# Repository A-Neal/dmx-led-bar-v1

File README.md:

# FPGA DMX Decoder and PWM Driver Written in Verilog

This project directory is uploaded as-is, and doesn't contain a lot of polish.

I used Apio to build the Verilog into a configuration for the FPGA, and developed
on a Lattice iCE40UP5k. You can use the underlying toolchain if you'd prefer, but
I recommend Apio if you aren't looking to get into the weeds and just want to
modify little bits of the Verilog or build it for a different FPGA.

If you are building exactly according to what's in this repo, you don't need to
have Apio or build the configuration. **hardware.bin** is the file that is already
built and padded to fit into the 2Mbit flash on the PCB.

To flash, I used a generic CH341A USB SPI flasher with `flashrom` to flash the
hardware.bin file.

`$ flashrom -p ch341a_spi -w hardware.bin`

This repo includes the KiCAD project for the PCB, as well as just the gerber files
for have the PCB produced if you don't want to do any mods.

The BOM file is a list of everything that goes on the PCB and a link to the part
on Mouser. It's inside the KiCAD project directory.

The LED strips I used get a little too hot for the channels I used when everything
is turned up, so I'm not going to recommend them. But I will link them anyway
because they're excellent for other uses or if you're building a beefier fixture
than these plans are for.

LED Strip I Used: https://a.co/d/0fOELpNe

Less Powerful Equivalent LED Strip: https://a.co/d/0jd0L9jr

Aluminum Diffuser Channels: https://a.co/d/0e7rKbcg

24V Power Supply: https://a.co/d/09dPfuRe

Use any 12-24V LED strip and power supply that you want so long as the strip fits
in the channels, and the power supply can push enough power comfortably.

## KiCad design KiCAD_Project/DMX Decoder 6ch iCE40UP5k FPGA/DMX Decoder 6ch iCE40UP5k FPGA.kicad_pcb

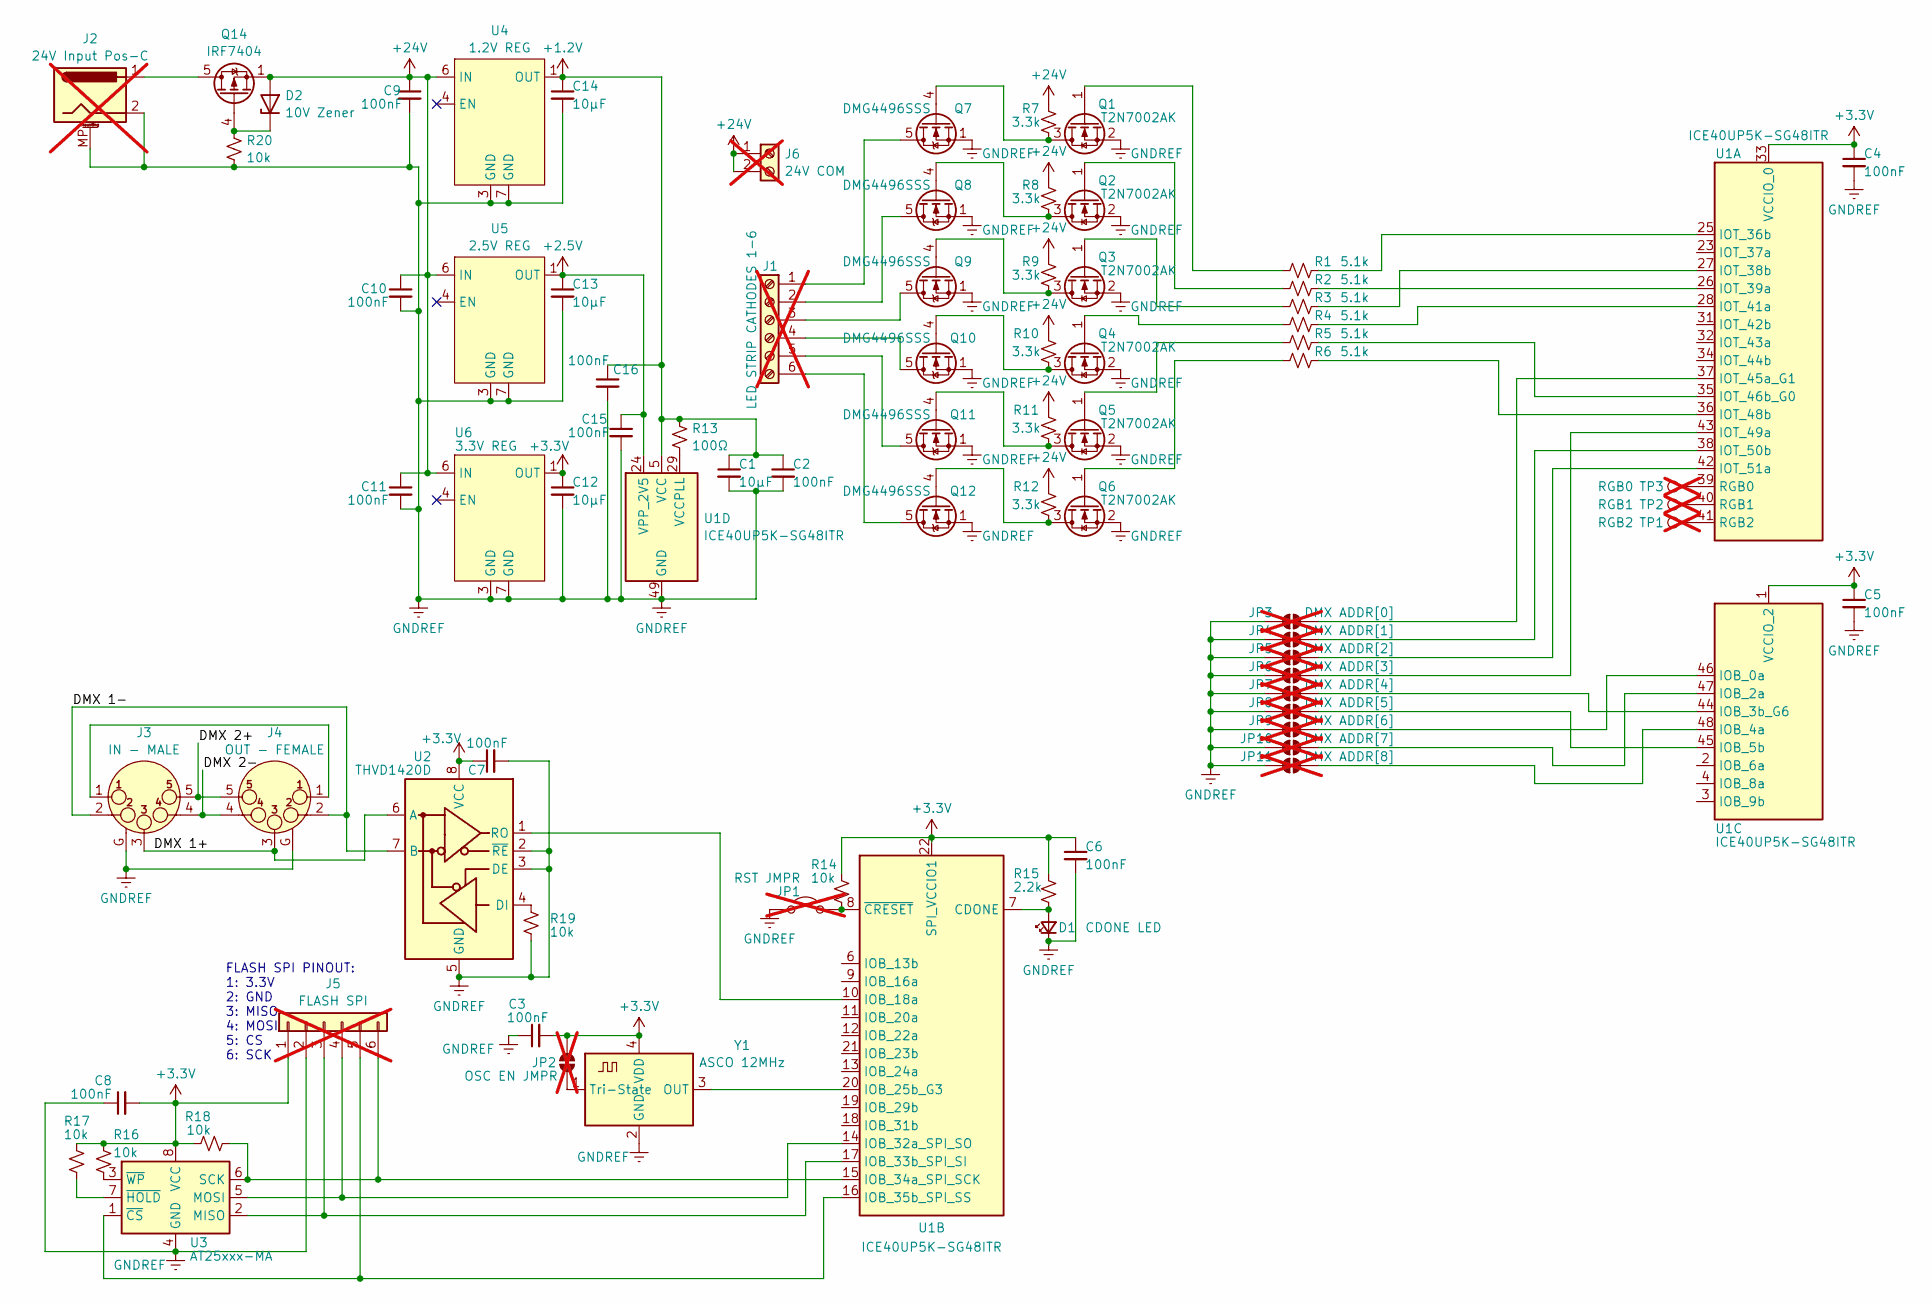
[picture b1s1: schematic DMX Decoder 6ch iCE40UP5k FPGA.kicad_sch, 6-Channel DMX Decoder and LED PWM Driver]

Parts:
C1, C12, C13, C14: 10μF; C_0603_1608Metric
C2, C3, C4, C5, C6, C7, C8, C9, C10, C11, C15, C16: 100nF; C_0603_1608Metric
D1: CDONE LED; LED_0805_2012Metric
D2: 10V Zener; D_SOD-123
J1: LED STRIP CATHODES 1-6; TerminalBlock_MaiXu_MX126-5.0-06P_1x06_P5.00mm; not fitted
J2: 24V Input Pos-C; BarrelJack_Horizontal_CUI_PJ-057A; not fitted
J3: IN - MALE; Jack_XLR_Neutrik_NC5MAV_Vertical
J4: OUT - FEMALE; Jack_XLR_Neutrik_NC5FAV_Vertical
J5: FLASH SPI; PinHeader_1x06_P2.54mm_Vertical; not fitted
J6: 24V COM; TerminalBlock_MaiXu_MX126-5.0-02P_1x02_P5.00mm; not fitted
JP1: RST JMPR; PinHeader_1x02_P1.27mm_Vertical; not fitted
JP2: OSC EN JMPR; SolderJumper-2_P1.3mm_Open_TrianglePad1.0x1.5mm; not fitted
JP3: DMX ADDR[0]; SolderJumper-2_P1.3mm_Open_TrianglePad1.0x1.5mm; not fitted
JP4: DMX ADDR[1]; SolderJumper-2_P1.3mm_Open_TrianglePad1.0x1.5mm; not fitted
JP5: DMX ADDR[2]; SolderJumper-2_P1.3mm_Open_TrianglePad1.0x1.5mm; not fitted
JP6: DMX ADDR[3]; SolderJumper-2_P1.3mm_Open_TrianglePad1.0x1.5mm; not fitted
JP7: DMX ADDR[4]; SolderJumper-2_P1.3mm_Open_TrianglePad1.0x1.5mm; not fitted
JP8: DMX ADDR[5]; SolderJumper-2_P1.3mm_Open_TrianglePad1.0x1.5mm; not fitted
JP9: DMX ADDR[6]; SolderJumper-2_P1.3mm_Open_TrianglePad1.0x1.5mm; not fitted
JP10: DMX ADDR[7]; SolderJumper-2_P1.3mm_Open_TrianglePad1.0x1.5mm; not fitted
JP11: DMX ADDR[8]; SolderJumper-2_P1.3mm_Open_TrianglePad1.0x1.5mm; not fitted
Q1, Q2, Q3, Q4, Q5, Q6: T2N7002AK; SOT-23
Q7, Q8, Q9, Q10, Q11, Q12: DMG4496SSS; SOIC-8_3.9x4.9mm_P1.27mm
Q14: IRF7404; SOIC-8_3.9x4.9mm_P1.27mm
R1, R2, R3, R4, R5, R6: 5.1k; R_0603_1608Metric
R7, R8, R9, R10, R11, R12: 3.3k; R_0603_1608Metric
R13: 100Ω; R_0603_1608Metric
R14, R16, R17, R18, R19, R20: 10k; R_0603_1608Metric
R15: 2.2k; R_0603_1608Metric
TP1: RGB2; Pin_D0.7mm_L6.5mm_W1.8mm_FlatFork; not fitted
TP2: RGB1; Pin_D0.7mm_L6.5mm_W1.8mm_FlatFork; not fitted
TP3: RGB0; Pin_D0.7mm_L6.5mm_W1.8mm_FlatFork; not fitted
U1: ICE40UP5K-SG48ITR; QFN-48-1EP_7x7mm_P0.5mm_EP5.6x5.6mm
U2: THVD1420D; SOIC-8_3.9x4.9mm_P1.27mm
U3: AT25xxx-MA; DFN-8-1EP_3x2mm_P0.5mm_EP1.75x1.45mm
U4: 1.2V REG; WSON-6-1EP_2x2mm_P0.65mm_EP1x1.6mm
U5: 2.5V REG; WSON-6-1EP_2x2mm_P0.65mm_EP1x1.6mm
U6: 3.3V REG; WSON-6-1EP_2x2mm_P0.65mm_EP1x1.6mm
Y1: ASCO 12MHz; Oscillator_SMD_Abracon_ASCO-4Pin_1.6x1.2mm

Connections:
+1.2V: C1.1, C2.1, C14.1, C16.1, R13.2, U1.5 (VCC), U1.30 (VCC), U4.1 (OUT)
+2.5V: C13.1, C15.1, U1.24 (VPP_2V5), U5.1 (OUT)
+3.3V: C3.2, C4.1, C5.1, C6.1, C7.1, C8.2, C12.1, J5.1, JP2.2 (B), R14.2, R15.2, R16.2, R17.2, R18.2, U1.1 (VCCIO_2), U1.22 (SPI_VCCIO1), U1.33 (VCCIO_0), U2.8 (VCC), U3.8 (VCC), U6.1 (OUT), Y1.4 (VDD)
+24V: C9.1, C10.1, C11.1, D2.2 (A), J6.1, J6.2, Q14.1 (S), Q14.2 (S), Q14.3 (S), R7.2, R8.2, R9.2, R10.2, R11.2, R12.2, U4.6 (IN), U5.6 (IN), U6.6 (IN)
/DMX 1+: J3.3, J4.3, U2.6 (A)
/DMX 1-: J3.2, J4.2, U2.7 (B)
/DMX 2+: J3.5, J4.5
/DMX 2-: J3.4 (P3), J4.4 (P3)
GNDREF: C1.2, C2.2, C3.1, C4.2, C5.2, C6.2, C7.2, C8.1, C9.2, C10.2, C11.2, C12.2, C13.2, C14.2, C15.2, C16.2, D1.1 (K), J2.2, J2.MP (MountPin_MP), J3.G, J4.G, J5.2, JP1.1 (A), JP3.1 (A), JP4.1 (A), JP5.1 (A), JP6.1 (A), JP7.1 (A), JP8.1 (A), JP9.1 (A), JP10.1 (A), JP11.1 (A), Q1.2 (S), Q2.2 (S), Q3.2 (S), Q4.2 (S), Q5.2 (S), Q6.2 (S), Q7.1 (S), Q7.2 (S), Q7.3 (S), Q8.1 (S), Q8.2 (S), Q8.3 (S), Q9.1 (S), Q9.2 (S), Q9.3 (S), Q10.1 (S), Q10.2 (S), Q10.3 (S), Q11.1 (S), Q11.2 (S), Q11.3 (S), Q12.1 (S), Q12.2 (S), Q12.3 (S), R19.1, R20.1, U1.49 (GND), U2.2 (~RE), U2.3 (DE), U2.5 (GND), U3.4 (GND), U3.9 (GND), U4.3 (GND), U4.7 (GND), U5.3 (GND), U5.7 (GND), U6.3 (GND), U6.7 (GND), Y1.2 (GND)
unnamed: D1.2 (A), R15.1, U1.7 (CDONE)
unnamed: D2.1 (K), Q14.4 (G), R20.2
unnamed: J1.1, Q7.5 (D), Q7.6 (D), Q7.7 (D), Q7.8 (D)
unnamed: J1.2, Q8.5 (D), Q8.6 (D), Q8.7 (D), Q8.8 (D)
unnamed: J1.3, Q9.5 (D), Q9.6 (D), Q9.7 (D), Q9.8 (D)
unnamed: J1.4, Q10.5 (D), Q10.6 (D), Q10.7 (D), Q10.8 (D)
unnamed: J1.5, Q11.5 (D), Q11.6 (D), Q11.7 (D), Q11.8 (D)
unnamed: J1.6, Q12.5 (D), Q12.6 (D), Q12.7 (D), Q12.8 (D)
unnamed: J2.1, Q14.5 (D), Q14.6 (D), Q14.7 (D), Q14.8 (D)
unnamed: J3.1, J4.1
unnamed: J5.3, U1.17 (IOB_33b_SPI_SI), U3.2 (MISO)
unnamed: J5.4, U1.14 (IOB_32a_SPI_SO), U3.5 (MOSI)
unnamed: J5.5, U1.16 (IOB_35b_SPI_SS), U3.1 (~CS)
unnamed: J5.6, R18.1, U1.15 (IOB_34a_SPI_SCK), U3.6 (SCK)
unnamed: JP1.2 (B), R14.1, U1.8 (~CRESET)
unnamed: JP2.1 (A), Y1.1 (Tri-State)
unnamed: JP3.2 (B), U1.37 (IOT_45a_G1)
unnamed: JP4.2 (B), U1.38 (IOT_50b)
unnamed: JP5.2 (B), U1.42 (IOT_51a)
unnamed: JP6.2 (B), U1.43 (IOT_49a)
unnamed: JP7.2 (B), U1.44 (IOB_3b_G6)
unnamed: JP8.2 (B), U1.45 (IOB_5b)
unnamed: JP9.2 (B), U1.46 (IOB_0a)
unnamed: JP10.2 (B), U1.47 (IOB_2a)
unnamed: JP11.2 (B), U1.48 (IOB_4a)
unnamed: Q1.3 (D), Q7.4 (G), R7.1
unnamed: Q1.1 (G), R1.1
unnamed: Q2.3 (D), Q8.4 (G), R8.1
unnamed: Q2.1 (G), R2.1
unnamed: Q3.3 (D), Q9.4 (G), R9.1
unnamed: Q3.1 (G), R3.1
unnamed: Q4.1 (G), R4.1
unnamed: Q5.1 (G), R5.1
unnamed: Q6.1 (G), R6.1
unnamed: Q4.3 (D), Q10.4 (G), R10.1
unnamed: Q5.3 (D), Q11.4 (G), R11.1
unnamed: Q6.3 (D), Q12.4 (G), R12.1
unnamed: R1.2, U1.25 (IOT_36b)
unnamed: R3.2, U1.27 (IOT_38b)
unnamed: R2.2, U1.26 (IOT_39a)
unnamed: R4.2, U1.28 (IOT_41a)
unnamed: R5.2, U1.35 (IOT_46b_G0)
unnamed: R6.2, U1.36 (IOT_48b)
unnamed: TP3.1 (1_1), U1.39 (RGB0)
unnamed: TP2.1 (1_1), U1.40 (RGB1)
unnamed: TP1.1 (1_1), U1.41 (RGB2)
unnamed: U1.10 (IOB_18a), U2.1 (RO)
unnamed: U1.20 (IOB_25b_G3), Y1.3 (OUT)
unnamed: R13.1, U1.29 (VCCPLL)
unnamed: R19.2, U2.4 (DI)
unnamed: R17.1, U3.7 (~HOLD)
unnamed: R16.1, U3.3 (~WP)

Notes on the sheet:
FLASH SPI PINOUT: 1: 3.3V 2: GND 3: MISO 4: MOSI 5: CS 6: SCK

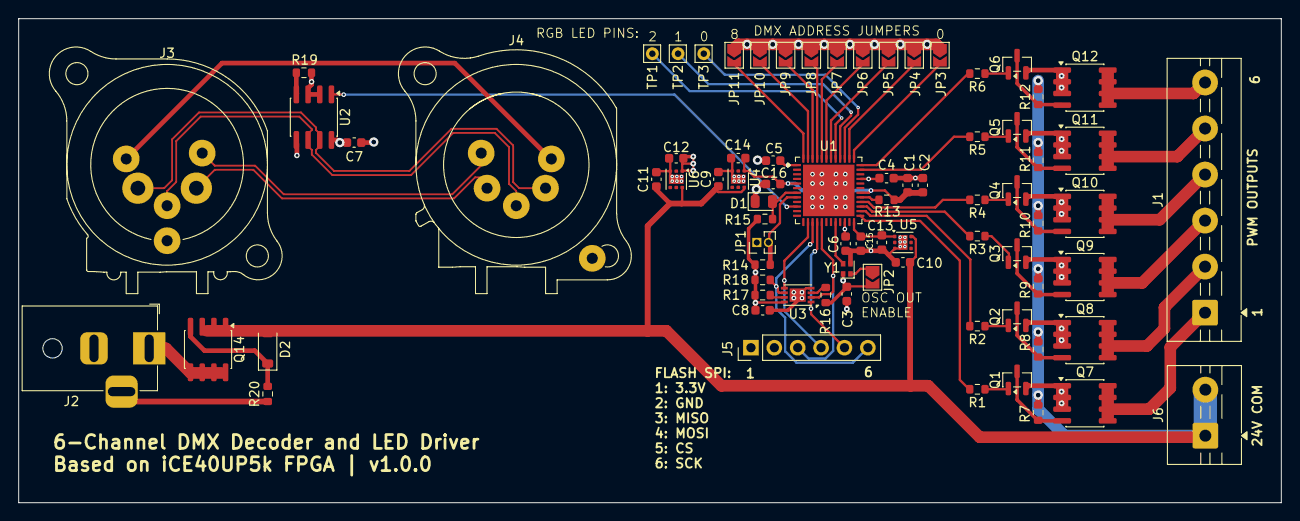
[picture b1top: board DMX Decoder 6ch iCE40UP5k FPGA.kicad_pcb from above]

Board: 4 copper layers, 137.2 x 52.6 mm, 78 parts (0 on the bottom side), 61 nets.

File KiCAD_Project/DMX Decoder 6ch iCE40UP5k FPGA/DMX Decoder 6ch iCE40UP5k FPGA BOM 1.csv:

"Reference","Qty","Value","Notes","Footprint","Manufacturer","MFR Part #","Mouser Part #"
"C1,C12,C13,C14","4","10μF",,"Capacitor_SMD:C_0603_1608Metric","Samsung Electro-Mechanics","CL10A106KP8NQSC","187-CL10A106KP8NQSC"
"C2,C3,C4,C5,C6,C7,C8,C9,C10,C11,C15,C16","12","100nF",,"Capacitor_SMD:C_0603_1608Metric","TAIYO YUDEN","UMK107BJ104KA-T","963-UMK107BJ104KA-T"
"D1","1","CDONE LED",,"LED_SMD:LED_0805_2012Metric","ROHM Semiconductor","SMLMN2BCTT86C","755-SMLMN2BCTT86C"
"D2","1","10V Zener",,"Diode_SMD:D_SOD-123","Vishay Semiconductor","BZT52C10-E3-18","78-BZT52C10-E3-18"
"J3","1","IN - MALE",,"Connector_Audio:Jack_XLR_Neutrik_NC5MAV_Vertical","Neutrik/REAN","RRX5M-B-023-0","568-RRX5M-B-023-0"
"J4","1","OUT - FEMALE",,"Connector_Audio:Jack_XLR_Neutrik_NC5FAV_Vertical","Neutrik/REAN","RRX5F-B-022-0","568-RRX5F-B-022-0"
"Q1,Q2,Q3,Q4,Q5,Q6","6","T2N7002AK N-MOSFET",,"Package_TO_SOT_SMD:SOT-23","Toshiba","T2N7002AK,LM","757-T2N7002AKLM"
"Q7,Q8,Q9,Q10,Q11,Q12","6","DMG4496SSS N-MOSFET",,"Package_SO:SOIC-8_3.9x4.9mm_P1.27mm","Diodes Incorporated","DMG4496SSS13","621-DMG4496SSS13"
"Q14","1","SI4435 P-MOSFET",,"Package_TO_SOT_SMD:SOT-23","Vishay / Siliconix","SI4435FDY-T1-GE3","78-SI4435FDY-T1-GE3 "
"R1,R2,R3,R4,R5,R6","6","5.1k",,"Resistor_SMD:R_0603_1608Metric","Panasonic","ERJ-U03F5101V","667-ERJ-U03F5101V"
"R7,R8,R9,R10,R11,R12","6","3.3k",,"Resistor_SMD:R_0603_1608Metric","Panasonic","ERJ-U03F3301V","667-ERJ-U03F3301V"
"R13","1","100Ω",,"Resistor_SMD:R_0603_1608Metric","Panasonic","ERJ-U03F1000V","667-ERJ-U03F1000V"
"R14,R16,R17,R18,R19,R20","6","10k",,"Resistor_SMD:R_0603_1608Metric","Panasonic","ERJ-U03F1002V","667-ERJ-U03F1002V"
"R15","1","2.2k",,"Resistor_SMD:R_0603_1608Metric","Panasonic","ERJ-U03F2201V","667-ERJ-U03F2201V"
"U1","1","ICE40UP5K-SG48ITR",,"Package_DFN_QFN:QFN-48-1EP_7x7mm_P0.5mm_EP5.6x5.6mm","Lattice","ICE40UP5K-SG48I","842-ICE40UP5K-SG48I"
"U2","1","THVD1420D",,"Package_SO:SOIC-8_3.9x4.9mm_P1.27mm","Texas Instruments","THVD1420DR","595-THVD1420DR"
"U3","1","AT25xxx-MA",,"Package_DFN_QFN:DFN-8-1EP_3x2mm_P0.5mm_EP1.75x1.45mm","Renesas Electronics","AT25EU0021AMAHNT","724-AT25EU0021AMAHNT  "
"U4","1","1.2V REG",,"Package_SON:WSON-6-1EP_2x2mm_P0.65mm_EP1x1.6mm","Texas Instruments","TPS70912DRVT","595-TPS70912DRVT"
"U5","1","2.5V REG",,"Package_SON:WSON-6-1EP_2x2mm_P0.65mm_EP1x1.6mm","Texas Instruments","TPS70925DRVR","595-TPS70925DRVR"
"U6","1","3.3V REG",,"Package_SON:WSON-6-1EP_2x2mm_P0.65mm_EP1x1.6mm","Texas Instruments","TPS70933DRVR","595-TPS70933DRVR"
"Y1","1","ASCO 12MHz",,"Oscillator:Oscillator_SMD_Abracon_ASCO-4Pin_1.6x1.2mm","Microchip","DSC1001DI5-012.0000 ","998-DSC1001DI5-012.0000 "
"J1","1","LED STRIP CATHODES 1-6","Generic Screw Terminals","TerminalBlock:TerminalBlock_MaiXu_MX126-5.0-06P_1x06_P5.00mm","GCT","TAH05-02-1-L-G ","640-TAH05-02-1-L-G "
"J2","1","24V Input Pos-C","Generic horizontal 5mm barrel jack","Custom:BarrelJack_Horizontal_CUI_PJ-057A","Same Sky (Formerly CUI)","PJ-057A ","490-PJ-057A "
"J5","1","FLASH SPI","Generic 0.100” pitch pin headers","Connector_PinHeader_2.54mm:PinHeader_1x06_P2.54mm_Vertical","Amphenol","77311-122-06LF","649-77311-122-06LF"
"J6","1","24V COM","Generic Screw Terminals","TerminalBlock:TerminalBlock_MaiXu_MX126-5.0-02P_1x02_P5.00mm","GCT","TAH05-02-1-L-G ","640-TAH05-02-1-L-G "
"JP1","1","RST JMPR","Generic 0.050” pitch pin headers","Connector_PinHeader_1.27mm:PinHeader_1x02_P1.27mm_Vertical","Samtec","TMS-102-21-G-S","200-TMS-102-21-G-S"

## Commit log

2026-04-14 Update README.md
    Fixed header in main README file
2026-04-14 Update README.md
    Fixed header in README in the 3D_Models directory
